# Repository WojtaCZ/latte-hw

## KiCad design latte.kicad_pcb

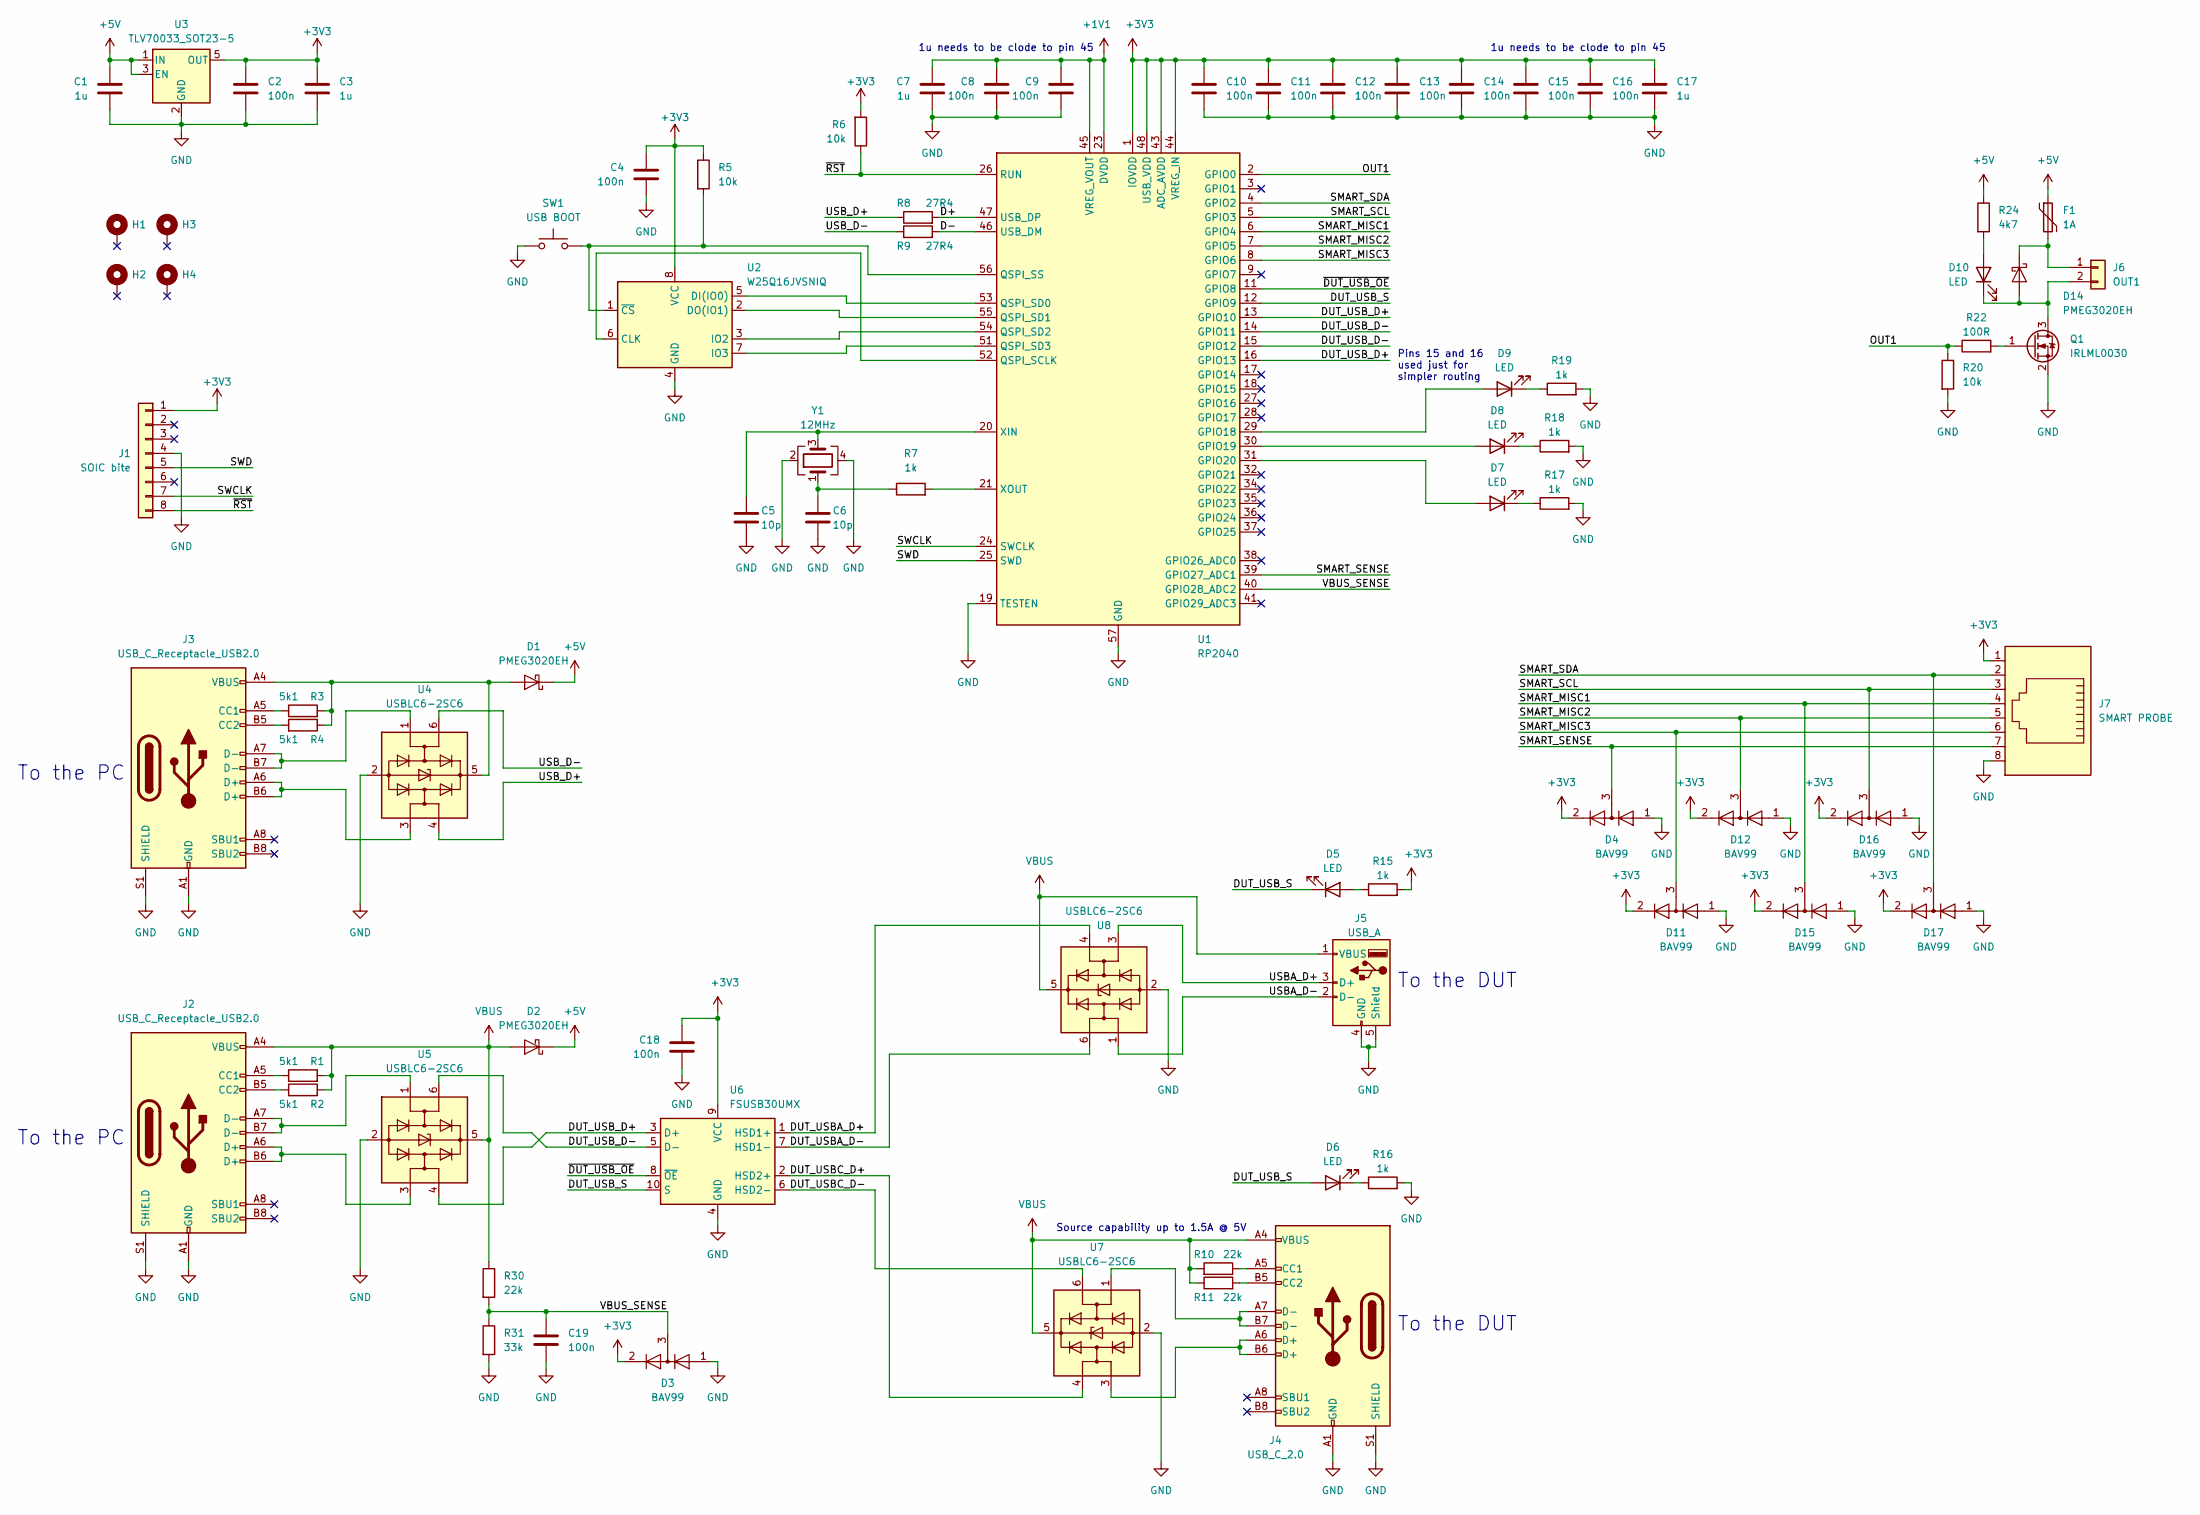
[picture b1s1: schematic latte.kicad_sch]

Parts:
C1, C3, C7, C17: 1u; C_0603_1608Metric
C2, C4, C8, C9, C10, C11, C12, C13, C14, C15, C16, C18, C19: 100n; C_0603_1608Metric
C5, C6: 10p; C_0603_1608Metric
D1, D2, D14: PMEG3020EH; D_SOD-123F
D3, D4, D11, D12, D15, D16, D17: BAV99; SOT-23
D5, D6, D7, D8, D9, D10: LED; LED_0603_1608Metric
F1: 1A; Fuse_0603_1608Metric
H1, H2, H3, H4: MountingHole_Pad; MountingHole_3.2mm_M3_Pad_Via
J1: SOIC bite; SOIC_clipProgSmall
J2, J3: USB_C_Receptacle_USB2.0; USB_C_Receptacle_XKB_U262-16XN-4BVC11
J4: USB_C_2.0; USB_C_Receptacle_XKB_U262-16XN-4BVC11
J5: USB_A; USB_A_Molex_67643_Horizontal
J6: OUT1; TerminalBlock_bornier-2_P5.08mm
J7: SMART PROBE; RJ45_Amphenol_54602-x08_Horizontal
Q1: IRLML0030; SOT-23
R1, R2, R3, R4: 5k1; R_0603_1608Metric
R5, R6, R20: 10k; R_0603_1608Metric
R7, R15, R16, R17, R18, R19: 1k; R_0603_1608Metric
R8, R9: 27R4; R_0603_1608Metric
R10, R11, R30: 22k; R_0603_1608Metric
R22: 100R; R_0603_1608Metric
R24: 4k7; R_0603_1608Metric
R31: 33k; R_0603_1608Metric
SW1: USB BOOT; SW_SPST_EVQPE1
U1: RP2040; QFN-56-1EP_7x7mm_P0.4mm_EP3.2x3.2mm
U2: W25Q16JVSNIQ; SOIC-8_3.9x4.9mm_P1.27mm
U3: TLV70033_SOT23-5; SOT-23-5
U4, U5, U7, U8: USBLC6-2SC6; SOT-23-6
U6: FSUSB30UMX; UQFN-10_1.3x1.8mm_P0.4mm
Y1: 12MHz; Crystal_SMD_3225-4Pin_3.2x2.5mm

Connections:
+1V1: C7.1, C8.1, C9.1, U1.23 (DVDD), U1.45 (VREG_VOUT), U1.50 (DVDD)
+3V3: C2.1, C3.1, C4.1, C10.1, C11.1, C12.1, C13.1, C14.1, C15.1, C16.1, C17.1, C18.1, D3.2 (A), D4.2 (A), D11.2 (A), D12.2 (A), D15.2 (A), D16.2 (A), D17.2 (A), J1.1, J7.1, R5.1, R6.2, R15.2, U1.1 (IOVDD), U1.10 (IOVDD), U1.22 (IOVDD), U1.33 (IOVDD), U1.42 (IOVDD), U1.43 (ADC_AVDD), U1.44 (VREG_IN), U1.48 (USB_VDD), U1.49 (IOVDD), U2.8 (VCC), U3.5 (OUT), U6.9 (VCC)
+5V: C1.2, D1.1 (K), D2.1 (K), F1.1, R24.1, U3.1 (IN), U3.3 (EN)
/D+: R8.2, U1.47 (USB_DP)
/D-: R9.2, U1.46 (USB_DM)
/DUT_USBA_D+: U6.1 (HSD1+), U8.4 (I/O2)
/DUT_USBA_D-: U6.7 (HSD1-), U8.6 (I/O1)
/DUT_USBC_D+: U6.2 (HSD2+), U7.4 (I/O2)
/DUT_USBC_D-: U6.6 (HSD2-), U7.6 (I/O1)
/DUT_USB_D+: U1.13 (GPIO10), U1.16 (GPIO13), U5.4 (I/O2), U6.3 (D+)
/DUT_USB_D-: U1.14 (GPIO11), U1.15 (GPIO12), U5.6 (I/O1), U6.5 (D-)
/DUT_USB_S: D5.1 (K), D6.2 (A), U1.12 (GPIO9), U6.10 (S)
/OUT1: R20.1, R22.1, U1.2 (GPIO0)
/SMART_MISC1: D15.3 (K), J7.4, U1.6 (GPIO4)
/SMART_MISC2: D12.3 (K), J7.5, U1.7 (GPIO5)
/SMART_MISC3: D11.3 (K), J7.6, U1.8 (GPIO6)
/SMART_SCL: D16.3 (K), J7.3, U1.5 (GPIO3)
/SMART_SDA: D17.3 (K), J7.2, U1.4 (GPIO2)
/SMART_SENSE: D4.3 (K), J7.7, U1.39 (GPIO27_ADC1)
/SWCLK: J1.7, U1.24 (SWCLK)
/SWD: J1.5, U1.25 (SWD)
/USBA_D+: J5.3 (D+), U8.3 (I/O2)
/USBA_D-: J5.2 (D-), U8.1 (I/O1)
/USB_D+: R8.1, U4.4 (I/O2)
/USB_D-: R9.1, U4.6 (I/O1)
/VBUS_SENSE: C19.1, D3.3 (K), R30.2, R31.1, U1.40 (GPIO28_ADC2)
/~DUT_USB_OE: U1.11 (GPIO8), U6.8 (~OE)
/~RST: J1.8, R6.1, U1.26 (RUN)
GND: C1.1, C2.2, C3.2, C4.2, C5.2, C6.2, C7.2, C8.2, C9.2, C10.2, C11.2, C12.2, C13.2, C14.2, C15.2, C16.2, C17.2, C18.2, C19.2, D3.1 (K), D4.1 (K), D11.1 (K), D12.1 (K), D15.1 (K), D16.1 (K), D17.1 (K), J1.4, J2.A1 (GND), J2.A12 (GND), J2.B1 (GND), J2.B12 (GND), J2.S1 (SHIELD), J3.A1 (GND), J3.A12 (GND), J3.B1 (GND), J3.B12 (GND), J3.S1 (SHIELD), J4.A1 (GND), J4.A12 (GND), J4.B1 (GND), J4.B12 (GND), J4.S1 (SHIELD), J5.4 (GND), J5.5 (Shield), J7.8, Q1.2 (S), R16.2, R17.2, R18.2, R19.2, R20.2, R31.2, SW1.1, U1.19 (TESTEN), U1.57 (GND), U2.4 (GND), U3.2 (GND), U4.2 (GND), U5.2 (GND), U6.4 (GND), U7.2 (GND), U8.2 (GND), Y1.2, Y1.4
unnamed: C5.1, U1.20 (XIN), Y1.3
unnamed: C6.1, R7.1, Y1.1
unnamed: D1.2 (A), J3.A4 (VBUS), J3.A9 (VBUS), J3.B4 (VBUS), J3.B9 (VBUS), R3.2, R4.1, U4.5 (VBUS)
unnamed: D5.2 (A), R15.1
unnamed: D6.1 (K), R16.1
unnamed: D7.1 (K), R17.1
unnamed: D7.2 (A), U1.31 (GPIO20)
unnamed: D8.1 (K), R18.1
unnamed: D8.2 (A), U1.30 (GPIO19)
unnamed: D9.1 (K), R19.1
unnamed: D9.2 (A), U1.29 (GPIO18)
unnamed: D10.1 (K), D14.2 (A), J6.2, Q1.3 (D)
unnamed: D10.2 (A), R24.2
unnamed: D14.1 (K), F1.2, J6.1
unnamed: J2.A5 (CC1), R1.1
unnamed: J2.A6 (D+), J2.B6 (D+), U5.3 (I/O2)
unnamed: J2.A7 (D-), J2.B7 (D-), U5.1 (I/O1)
unnamed: J2.B5 (CC2), R2.2
unnamed: J3.A5 (CC1), R3.1
unnamed: J3.A6 (D+), J3.B6 (D+), U4.3 (I/O2)
unnamed: J3.A7 (D-), J3.B7 (D-), U4.1 (I/O1)
unnamed: J3.B5 (CC2), R4.2
unnamed: J4.A5 (CC1), R10.1
unnamed: J4.A6 (D+), J4.B6 (D+), U7.3 (I/O2)
unnamed: J4.A7 (D-), J4.B7 (D-), U7.1 (I/O1)
unnamed: J4.B5 (CC2), R11.2
unnamed: Q1.1 (G), R22.2
unnamed: R5.2, SW1.2, U1.56 (QSPI_SS), U2.1 (~CS)
unnamed: R7.2, U1.21 (XOUT)
unnamed: U1.51 (QSPI_SD3), U2.7 (IO3)
unnamed: U1.52 (QSPI_SCLK), U2.6 (CLK)
unnamed: U1.53 (QSPI_SD0), U2.5 (DI(IO0))
unnamed: U1.54 (QSPI_SD2), U2.3 (IO2)
unnamed: U1.55 (QSPI_SD1), U2.2 (DO(IO1))
VBUS: D2.2 (A), J2.A4 (VBUS), J2.A9 (VBUS), J2.B4 (VBUS), J2.B9 (VBUS), J4.A4 (VBUS), J4.A9 (VBUS), J4.B4 (VBUS), J4.B9 (VBUS), J5.1 (VBUS), R1.2, R2.1, R10.2, R11.1, R30.1, U5.5 (VBUS), U7.5 (VBUS), U8.5 (VBUS)

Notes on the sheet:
1u needs to be clode to pin 45
To the PC
Pins 15 and 16 used just for simpler routing
Source capability up to 1.5A @ 5V
To the DUT

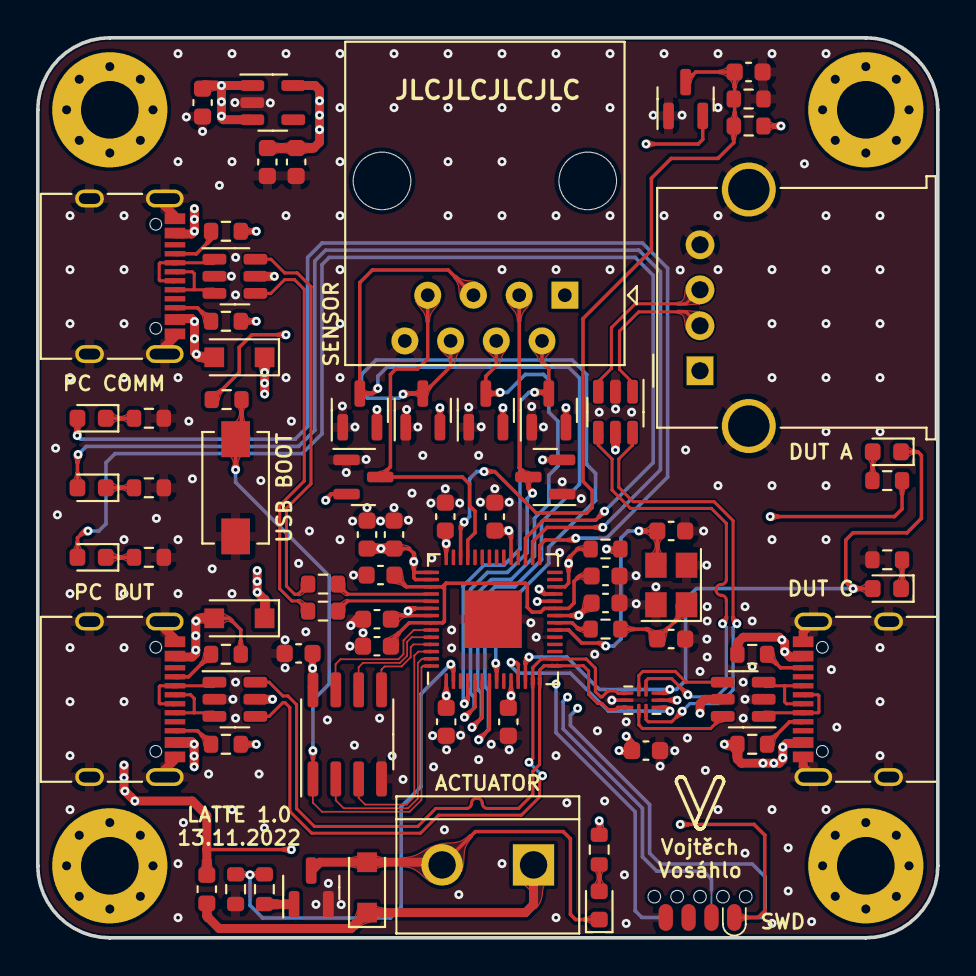
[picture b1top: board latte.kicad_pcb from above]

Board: 4 copper layers, 50.0 x 50.0 mm, 79 parts (0 on the bottom side), 64 nets.

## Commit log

2022-11-07 Schematic done
2022-11-07 Rough layout done
2022-11-08 Fixed project structure
2022-11-08 Diff pair routing done
2022-11-13 Routing done
2022-11-13 Added via stitching
2022-11-18 Added logo
2022-11-24 Finalized for production
2023-03-11 Fixed switched D+/D- on PC DUT USB connector
2023-11-26 Sync
